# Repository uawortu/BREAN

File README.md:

# BREAN
## Custom esp32cam
Video : [I made a CUSTOM ESP32CAM！ - YouTube](https://www.youtube.com/watch?v=4ouxIVEyoTg)

### Information provided
* 3dmodels
* Images and renders
* Gerber files
* My code and code used
* Print files

# I'll give a proper description in time

#### BOM/PART LIST 
[Google sheets](https://docs.google.com/spreadsheets/d/1bDLKCBJ3s3EqrjJLohymS0VN41cs3GhnOAAEiNUEGFg/edit?usp=sharing)
[CSV file download](https://github.com/user-attachments/files/17560012/BOM.csv)

##### BREAN=beans+bread

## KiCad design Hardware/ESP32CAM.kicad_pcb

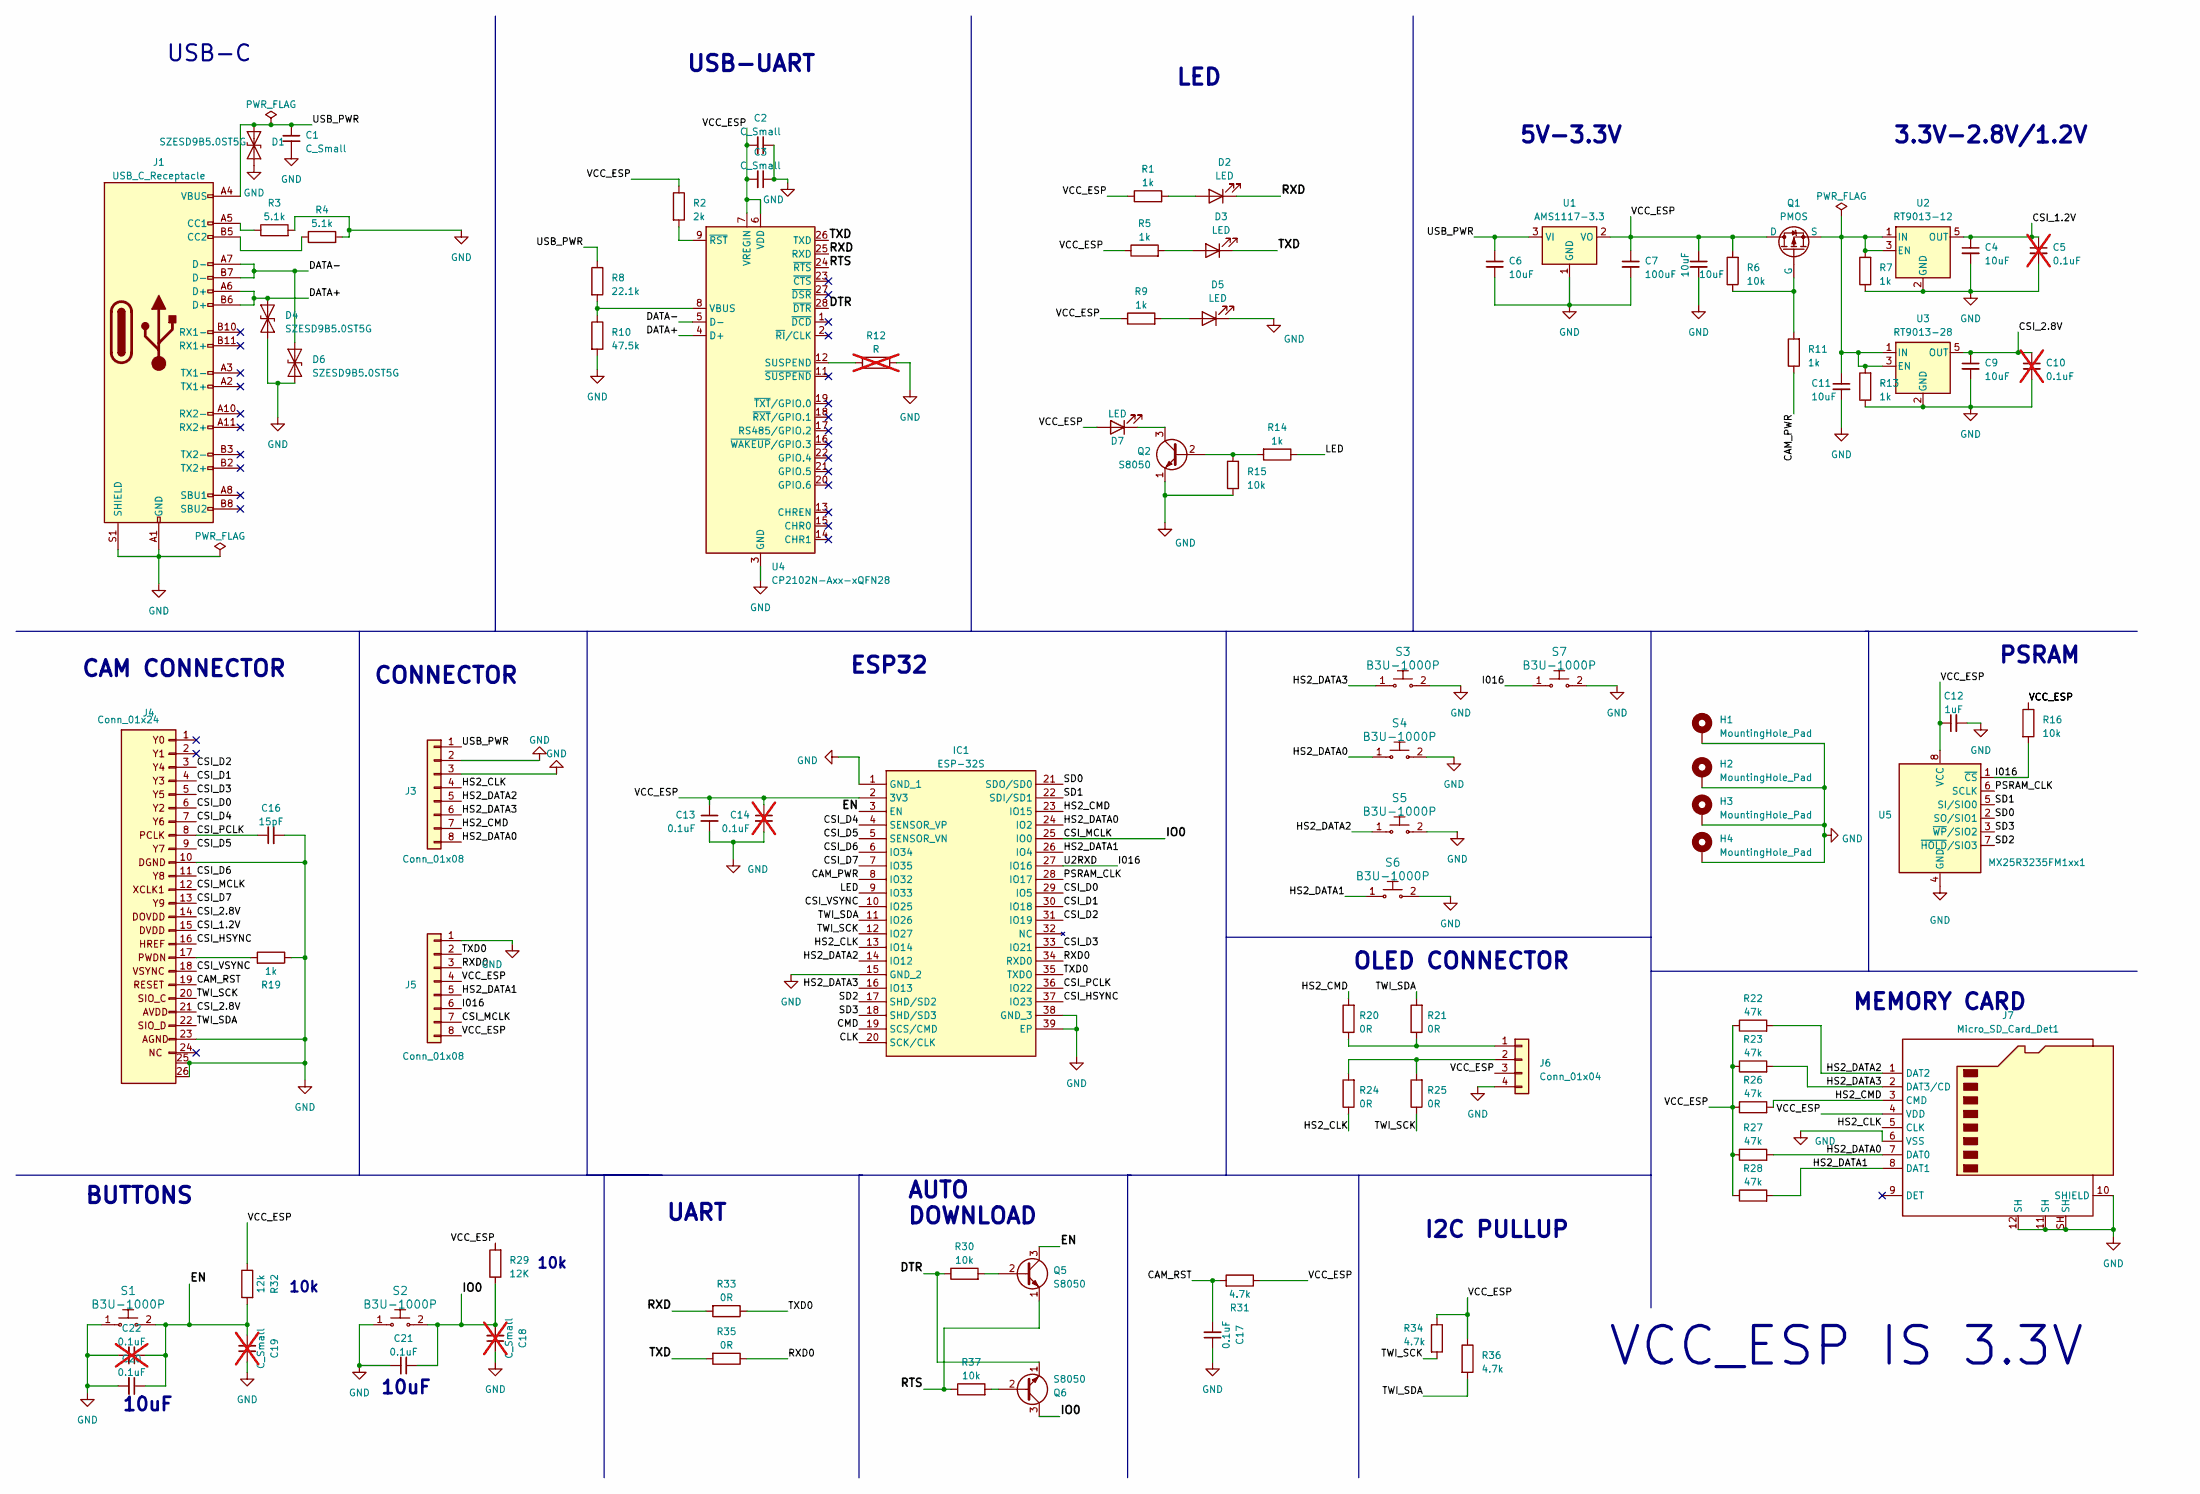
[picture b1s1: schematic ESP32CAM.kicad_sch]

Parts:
10uF: 10uF; C_0603_1608Metric_Pad1.08x0.95mm_HandSolder
C1, C2, C3: C_Small; C_0603_1608Metric_Pad1.08x0.95mm_HandSolder
C4, C6, C9, C11: 10uF; C_0603_1608Metric_Pad1.08x0.95mm_HandSolder
C5, C10, C14, C22: 0.1uF; C_0603_1608Metric_Pad1.08x0.95mm_HandSolder; not fitted
C7: 100uF; CP_EIA-3528-15_AVX-H_Pad1.50x2.35mm_HandSolder
C12: 1uF; C_0603_1608Metric_Pad1.08x0.95mm_HandSolder
C13, C17, C20, C21: 0.1uF; C_0603_1608Metric_Pad1.08x0.95mm_HandSolder
C16: 15pF; C_0603_1608Metric_Pad1.08x0.95mm_HandSolder
C18, C19: C_Small; C_0603_1608Metric_Pad1.08x0.95mm_HandSolder; not fitted
D1, D4, D6: SZESD9B5.0ST5G; D_SOD-923
D2, D3, D5: LED; LED_0603_1608Metric_Pad1.05x0.95mm_HandSolder
D7: LED; LED_Kingbright_AAA3528ESGCT
H1, H2, H3, H4: MountingHole_Pad; MountingHole_3.7mm
IC1: ESP-32S; ESP32S; Manufacturer_Part_Number ESP-32S; Mouser Part Number N/A
J1: USB_C_Receptacle; USB_C_Receptacle_GCT_USB4105-xx-A_16P_TopMnt_Horizontal
J3, J5: Conn_01x08; PinHeader_1x08_P2.54mm_Vertical
J4: Conn_01x24; Hirose_FH12-24S-0.5SH_1x24-1MP_P0.50mm_Horizontal
J6: Conn_01x04; PinSocket_1x04_P2.54mm_Vertical
J7: Micro_SD_Card_Det1; J_SD_Card-micro_socket_A
Q1: PMOS; SOT-23-3
Q2, Q5, Q6: S8050; SOT-23-3
R1, R5, R7, R9, R11, R13, R14, R19: 1k; R_0603_1608Metric_Pad0.98x0.95mm_HandSolder
R2: 2k; R_0603_1608Metric_Pad0.98x0.95mm_HandSolder
R3, R4: 5.1k; R_0603_1608Metric_Pad0.98x0.95mm_HandSolder
R6, R15, R16, R30, R37: 10k; R_0603_1608Metric_Pad0.98x0.95mm_HandSolder
R8: 22.1k; R_0603_1608Metric_Pad0.98x0.95mm_HandSolder
R10: 47.5k; R_0603_1608Metric_Pad0.98x0.95mm_HandSolder
R12: R; R_0603_1608Metric_Pad0.98x0.95mm_HandSolder; not fitted
R20, R21, R24, R25, R33, R35: 0R; R_0603_1608Metric_Pad0.98x0.95mm_HandSolder
R22, R23, R26, R27, R28: 47k; R_0603_1608Metric_Pad0.98x0.95mm_HandSolder
R29: 12K; R_0603_1608Metric_Pad0.98x0.95mm_HandSolder
R31, R34, R36: 4.7k; R_0603_1608Metric_Pad0.98x0.95mm_HandSolder
R32: 12k; R_0603_1608Metric_Pad0.98x0.95mm_HandSolder
S1, S2, S3: B3U-1000P; SW_Tactile_SPST_NO_Straight_CK_PTS636Sx25SMTRLFS; MPN B3U-1000P; Digi-Key_PN SW1020CT-ND
S4, S5, S6, S7: B3U-1000P; Panasonic_EVQPUM_EVQPUD; MPN B3U-1000P; Digi-Key_PN SW1020CT-ND
U1: AMS1117-3.3; SOT-223-3_TabPin2
U2: RT9013-12; SOT-23-5
U3: RT9013-28; SOT-23-5
U4: CP2102N-Axx-xQFN28; QFN-28-1EP_5x5mm_P0.5mm_EP3.35x3.35mm
U5: MX25R3235FM1xx1; SOP-8_3.9x4.9mm_P1.27mm

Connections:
/CAM_PWR: IC1.8 (IO32), R11.1
/CAM_RST: C17.2, J4.19, R31.2
/CLK: IC1.20 (SCK/CLK)
/CMD: IC1.19 (SCS/CMD)
/CSI_1.2V: C4.1, C5.1, J4.15, U2.5 (OUT)
/CSI_2.8V: C9.1, C10.1, J4.14, J4.21, U3.5 (OUT)
/CSI_D0: IC1.29 (IO5), J4.6
/CSI_D1: IC1.30 (IO18), J4.4
/CSI_D2: IC1.31 (IO19), J4.3
/CSI_D3: IC1.33 (IO21), J4.5
/CSI_D4: IC1.4 (SENSOR_VP), J4.7
/CSI_D5: IC1.5 (SENSOR_VN), J4.9
/CSI_D6: IC1.6 (IO34), J4.11
/CSI_D7: IC1.7 (IO35), J4.13
/CSI_HSYNC: IC1.37 (IO23), J4.16
/CSI_MCLK: C18.2, C21.1, IC1.25 (IO0), J4.12, J5.7, Q6.3 (C), R29.1, S2.2
/CSI_PCLK: C16.1, IC1.36 (IO22), J4.8
/CSI_VSYNC: IC1.10 (IO25), J4.18
/DATA+: D4.2 (A2), J1.A6 (D+), J1.B6 (D+), U4.4 (D+)
/DATA-: D6.2 (A2), J1.A7 (D-), J1.B7 (D-), U4.5 (D-)
/DTR: Q6.1 (E), R30.1, U4.28 (~DTR)
/EN: C19.2, C20.1, C22.1, IC1.3 (EN), Q5.3 (C), R32.2, S1.2
/HS2_CLK: IC1.13 (IO14), J3.4, J7.5 (CLK), R24.1
/HS2_CMD: IC1.23 (IO15), J3.7, J7.3 (CMD), R20.2, R26.2
/HS2_DATA0: IC1.24 (IO2), J3.8, J7.7 (DAT0), R27.2, S4.1
/HS2_DATA1: IC1.26 (IO4), J5.5, J7.8 (DAT1), R28.2, S6.1
/HS2_DATA2: IC1.14 (IO12), J3.5, J7.1 (DAT2), R22.2, S5.1
/HS2_DATA3: IC1.16 (IO13), J3.6, J7.2 (DAT3/CD), R23.2, S3.1
/I016: IC1.27 (IO16), J5.6, R16.2, S7.1, U5.1 (~CS)
/LED: IC1.9 (IO33), R14.1
/PSRAM_CLK: IC1.28 (IO17), U5.6 (SCLK)
/RTS: Q5.1 (E), R37.1, U4.24 (~RTS)
/RXD: D2.1 (K), R33.2, U4.25 (RXD)
/RXD0: IC1.34 (RXD0), J5.3, R35.1
/SD0: IC1.21 (SDO/SD0), U5.2 (SO/SIO1)
/SD1: IC1.22 (SDI/SD1), U5.5 (SI/SIO0)
/SD2: IC1.17 (SHD/SD2), U5.7 (~HOLD/SIO3)
/SD3: IC1.18 (SHD/SD3), U5.3 (~WP/SIO2)
/TWI_SCK: IC1.12 (IO27), J4.20, R25.1, R34.2
/TWI_SDA: IC1.11 (IO26), J4.22, R21.2, R36.2
/TXD: D3.1 (K), R35.2, U4.26 (TXD)
/TXD0: IC1.35 (TXDO), J5.2, R33.1
/USB_PWR: C1.1, C6.1, D1.2 (A2), J1.A4 (VBUS), J1.A9 (VBUS), J1.B4 (VBUS), J1.B9 (VBUS), J3.1, R8.1, U1.3 (VI)
/VCC_ESP: 10uF.1, C2.2, C3.2, C7.1, C12.1, C13.1, C14.1, D7.2 (A), IC1.2 (3V3), J5.4, J5.8, J6.3, J7.4 (VDD), Q1.1 (D), R1.1, R2.1, R5.1, R6.2, R9.1, R16.1, R22.1, R23.1, R26.1, R27.1, R28.1, R29.2, R31.1, R32.1, R34.1, R36.1, U1.2 (VO), U4.6 (VDD), U4.7 (VREGIN), U5.8 (VCC); also elsewhere on the board
GND: 10uF.2, C1.2, C2.1, C3.1, C4.2, C5.2, C6.2, C7.2, C9.2, C10.2, C11.2, C12.2, C13.2, C14.2, C16.2, C17.1, C18.1, C19.1, C20.2, C21.2, C22.2, D1.1 (A1), D4.1 (A1), D5.1 (K), D6.1 (A1), H1.1, H2.1, H3.1, H4.1, IC1.1 (GND_1), IC1.15 (GND_2), IC1.38 (GND_3), IC1.39 (EP), J1.A1 (GND), J1.A12 (GND), J1.B1 (GND), J1.B12 (GND), J1.S1 (SHIELD), J3.2, J3.3, J4.10, J4.23, J4.25 (GND), J4.26 (GND), J5.1, J6.4, J7.6 (VSS), J7.10 (SHIELD), J7.11 (SH), J7.12 (SH), J7.SH, Q2.1 (E), R3.2, R4.2, R7.1, R10.2, R12.2, R13.1, R15.1, R19.1, S1.1, S2.1, S3.2, S4.2, S5.2, S6.2, S7.2, U1.1 (GND), U2.2 (GND), U3.2 (GND), U4.3 (GND), U4.29 (GND), U5.4 (GND); also elsewhere on the board
unnamed: C11.1, Q1.3 (S), R7.2, R13.2, U2.1 (IN), U2.3 (EN), U3.1 (IN), U3.3 (EN)
unnamed: D2.2 (A), R1.2
unnamed: D3.2 (A), R5.2
unnamed: D5.2 (A), R9.2
unnamed: D7.1 (K), Q2.3 (C)
unnamed: J1.A5 (CC1), R3.1
unnamed: J1.B5 (CC2), R4.1
unnamed: J4.17, R19.2
unnamed: J6.1, R20.1, R21.1
unnamed: J6.2, R24.2, R25.2
unnamed: Q1.2 (G), R6.1, R11.2
unnamed: Q2.2 (B), R14.2, R15.2
unnamed: Q5.2 (B), R30.2
unnamed: Q6.2 (B), R37.2
unnamed: R12.1, U4.12 (SUSPEND)
unnamed: R8.2, R10.1, U4.8 (VBUS)
unnamed: R2.2, U4.9 (~RST)

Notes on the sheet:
VCC_ESP IS 3.3V
5V-3.3V
CAM CONNECTOR
10uF
3.3V-2.8V/1.2V
LED
ESP32
USB-UART
OLED CONNECTOR
10k
UART
BUTTONS
PSRAM
CONNECTOR
I2C PULLUP
MEMORY CARD
USB-C
AUTO DOWNLOAD

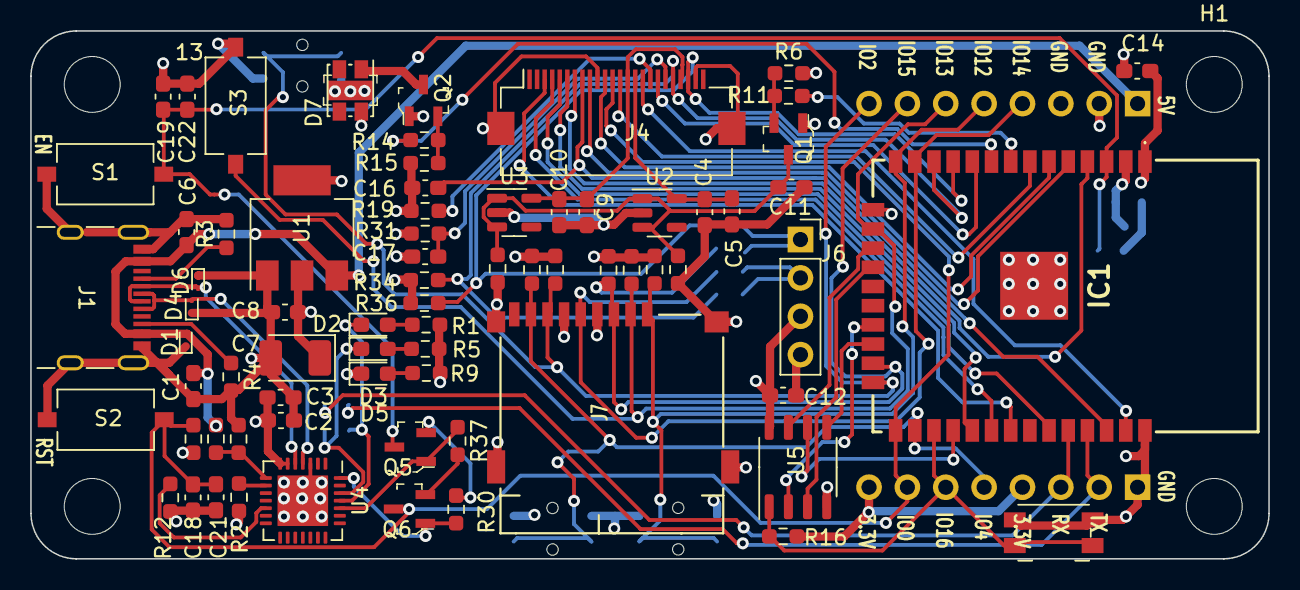
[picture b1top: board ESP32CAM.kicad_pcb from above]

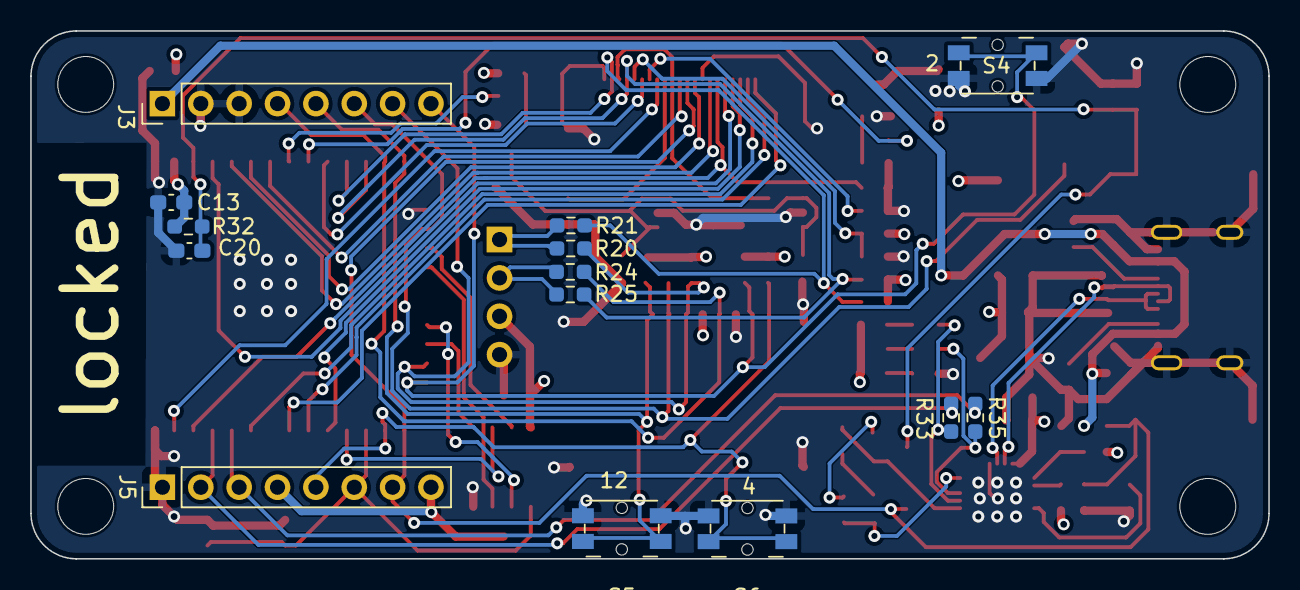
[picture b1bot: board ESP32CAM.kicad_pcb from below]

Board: 4 copper layers, 82.0 x 35.0 mm, 90 parts (14 on the bottom side), 60 nets.

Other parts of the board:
C8: 10uF; C_0603_1608Metric_Pad1.08x0.95mm_HandSolder

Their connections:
/VCC_ESP: C8.1; also elsewhere on the board
GND: C8.2; also elsewhere on the board

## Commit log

2023-11-01 added pong game
    added pong game to test
2024-01-21 upload
2024-10-29 added partlist
    added link to the parts list in README.md
2024-10-29 added google sheets link and csv file link for the BOM/PARTS LIST
2024-10-29 added kicad design files and pdf showing schematic
